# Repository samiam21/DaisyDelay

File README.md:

# DaisyPedal

To get started with programming the ElectroSmith Daisy in Arduino [Getting Started (Arduino Edition) Wiki page!](https://github.com/electro-smith/DaisyWiki/wiki/1a.-Getting-Started-(Arduino-Edition))

## Environment

This project is designed to build with VSCode using the Arduino extension.  It _should_ also build in the Arduino IDE but is untested.

* VS Code - https://code.visualstudio.com/
* VS Code Arduino Extension - https://marketplace.visualstudio.com/items?itemName=vsciot-vscode.vscode-arduino

## Configuration

The files within the .vscode folder may need updated for your environment.  Below is a description of each and what you may need to change.

### arduino.json

This file contains information on the board and connections.

Notes:
* The "output" definition allows VS Code to re-use compiled libraries, rather than needing to compile them every time.
* You will likely need to update the port to reference the COM port on your machine, for when the device is running, not in program mode.
* The "sketch" definition defines which Arduino sketch is compiled.  This project only has a top-level sketch so this should not be modified.

### c_cpp_properties.json

This file contains include paths and other information required for compiling C/C++ code.

Notes:
* You may need to update the "includePath" and "forcedInclude" definitions to point to the correct locations on your machine.

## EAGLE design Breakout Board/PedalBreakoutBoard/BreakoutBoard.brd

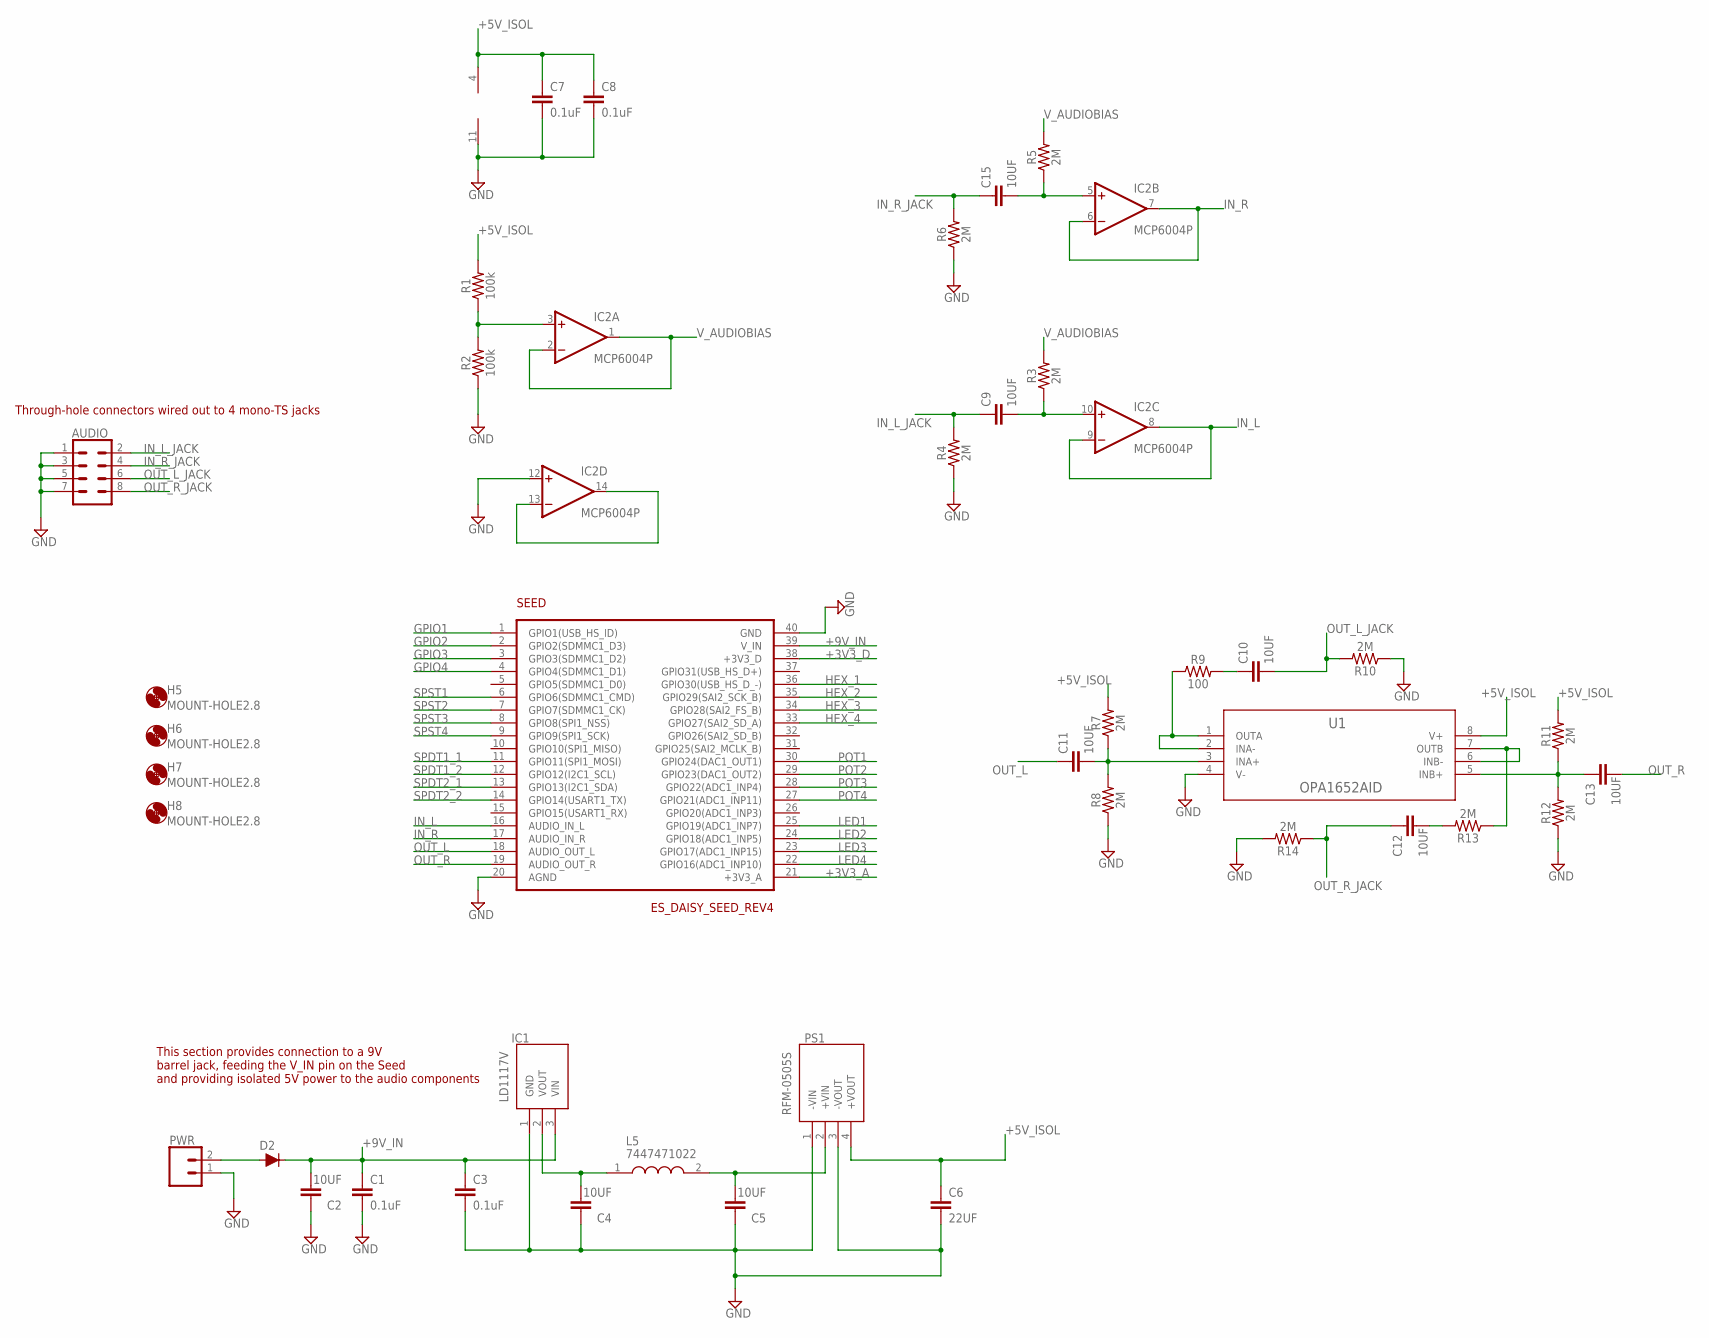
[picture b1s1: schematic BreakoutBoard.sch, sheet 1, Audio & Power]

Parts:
AUDIO: CONN_04X2; 2X4
C1, C3, C7, C8: 0.1uF; CAP-PTH-SMALL-KIT
C2, C4, C5, C9, C10, C11, C12, C13, C15: 10UF; CAP-PTH-SMALL-KIT
C6: 22UF; CAP-PTH-SMALL-KIT
D2: 200mA/100V/1V; DIODE-1N4148
H5, H6, H7, H8: MOUNT-HOLE2.8; 2,8
IC1: LD1117V; TO255P460X1020X2008-3P
IC2: MCP6004P; DIL14
L5: 7447471022; WE-TIS_111190
PS1: RFM-0505S; RFM0505S
PWR: CONN_02; 1X02
R1, R2: 100k; AXIAL-0.3
R3, R4, R5, R6, R7, R8, R10, R11, R12, R13, R14: 2M; AXIAL-0.3
R9: 100; AXIAL-0.3
SEED: ES_DAISY_SEED_REV4; ES_DAISY_SEED
U1: OPA1652AID; D8

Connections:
+3V3_A: SEED.21 (+3V3_A); also elsewhere on the board
+3V3_D: SEED.38 (+3V3_D)
+5V_ISOL: C6.1, C7.1, C8.1, IC2.4 (V+), PS1.4 (+VOUT), R1.P$2 (2), R7.P$2 (2), R11.P$2 (2), U1.8 (V+)
+9V_IN: C1.1, C2.2, C3.1, D2.C, IC1.3 (VIN), SEED.39 (V_IN)
GND: AUDIO.1, AUDIO.3, AUDIO.5, AUDIO.7, C1.2, C2.1, C3.2, C4.1, C5.1, C6.2, C7.2, C8.2, IC1.1 (GND), IC2.11 (V-), IC2.12 (+IN), PS1.1 (-VIN), PS1.3 (-VOUT), PWR.1, R2.P$1 (1), R4.P$1 (1), R6.P$1 (1), R8.P$1 (1), R10.P$1 (1), R12.P$1 (1), R14.P$2 (2), SEED.20 (AGND), SEED.40 (GND), U1.4 (V-); also elsewhere on the board
GPIO1: SEED.1 (GPIO1(USB_HS_ID)); also elsewhere on the board
GPIO2: SEED.2 (GPIO2(SDMMC1_D3)); also elsewhere on the board
GPIO3: SEED.3 (GPIO3(SDMMC1_D2)); also elsewhere on the board
GPIO4: SEED.4 (GPIO4(SDMMC1_D1)); also elsewhere on the board
HEX_1: SEED.36 (GPIO30(USB_HS_D_-)); also elsewhere on the board
HEX_2: SEED.35 (GPIO29(SAI2_SCK_B)); also elsewhere on the board
HEX_3: SEED.34 (GPIO28(SAI2_FS_B)); also elsewhere on the board
HEX_4: SEED.33 (GPIO27(SAI2_SD_A)); also elsewhere on the board
IN_L: IC2.8 (OUT), IC2.9 (-IN), SEED.16 (AUDIO_IN_L)
IN_L_JACK: AUDIO.2, C9.1, R4.P$2 (2)
IN_R: IC2.6 (-IN), IC2.7 (OUT), SEED.17 (AUDIO_IN_R)
IN_R_JACK: AUDIO.4, C15.1, R6.P$2 (2)
LED1: SEED.25 (GPIO19(ADC1_INP7)); also elsewhere on the board
LED2: SEED.24 (GPIO18(ADC1_INP5)); also elsewhere on the board
LED3: SEED.23 (GPIO17(ADC1_INP15)); also elsewhere on the board
LED4: SEED.22 (GPIO16(ADC1_INP10)); also elsewhere on the board
unnamed: D2.A, PWR.2
unnamed: IC2.3 (+IN), R1.P$1 (1), R2.P$2 (2)
unnamed: C5.2, L5.2, PS1.2 (+VIN)
unnamed: C4.2, IC1.2 (VOUT), L5.1
unnamed: C9.2, IC2.10 (+IN), R3.P$1 (1)
unnamed: IC2.13 (-IN), IC2.14 (OUT)
unnamed: C15.2, IC2.5 (+IN), R5.P$1 (1)
unnamed: C11.2, R7.P$1 (1), R8.P$2 (2), U1.3 (INA+)
unnamed: R9.P$1 (1), U1.1 (OUTA), U1.2 (INA-)
unnamed: C10.1, R9.P$2 (2)
unnamed: C13.1, R11.P$1 (1), R12.P$2 (2), U1.5 (INB+)
unnamed: C12.2, R13.P$2 (2)
unnamed: R13.P$1 (1), U1.6 (INB-), U1.7 (OUTB)
OUT_L: C11.1, SEED.18 (AUDIO_OUT_L)
OUT_L_JACK: AUDIO.6, C10.2, R10.P$2 (2)
OUT_R: C13.2, SEED.19 (AUDIO_OUT_R)
OUT_R_JACK: AUDIO.8, C12.1, R14.P$1 (1)
POT1: SEED.30 (GPIO24(DAC1_OUT1)); also elsewhere on the board
POT2: SEED.29 (GPIO23(DAC1_OUT2)); also elsewhere on the board
POT3: SEED.28 (GPIO22(ADC1_INP4)); also elsewhere on the board
POT4: SEED.27 (GPIO21(ADC1_INP11)); also elsewhere on the board
SPDT1_1: SEED.11 (GPIO11(SPI1_MOSI)); also elsewhere on the board
SPDT1_2: SEED.12 (GPIO12(I2C1_SCL)); also elsewhere on the board
SPDT2_1: SEED.13 (GPIO13(I2C1_SDA)); also elsewhere on the board
SPDT2_2: SEED.14 (GPIO14(USART1_TX)); also elsewhere on the board
SPST1: SEED.6 (GPIO6(SDMMC1_CMD)); also elsewhere on the board
SPST2: SEED.7 (GPIO7(SDMMC1_CK)); also elsewhere on the board
SPST3: SEED.8 (GPIO8(SPI1_NSS)); also elsewhere on the board
SPST4: SEED.9 (GPIO9(SPI1_SCK)); also elsewhere on the board
V_AUDIOBIAS: IC2.1 (OUT), IC2.2 (-IN), R3.P$2 (2), R5.P$2 (2)

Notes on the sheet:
Through-hole connectors wired out to 4 mono-TS jacks
This section provides connection to a 9V barrel jack, feeding the V_IN pin on the Seed and providing isolated 5V power to the audio components

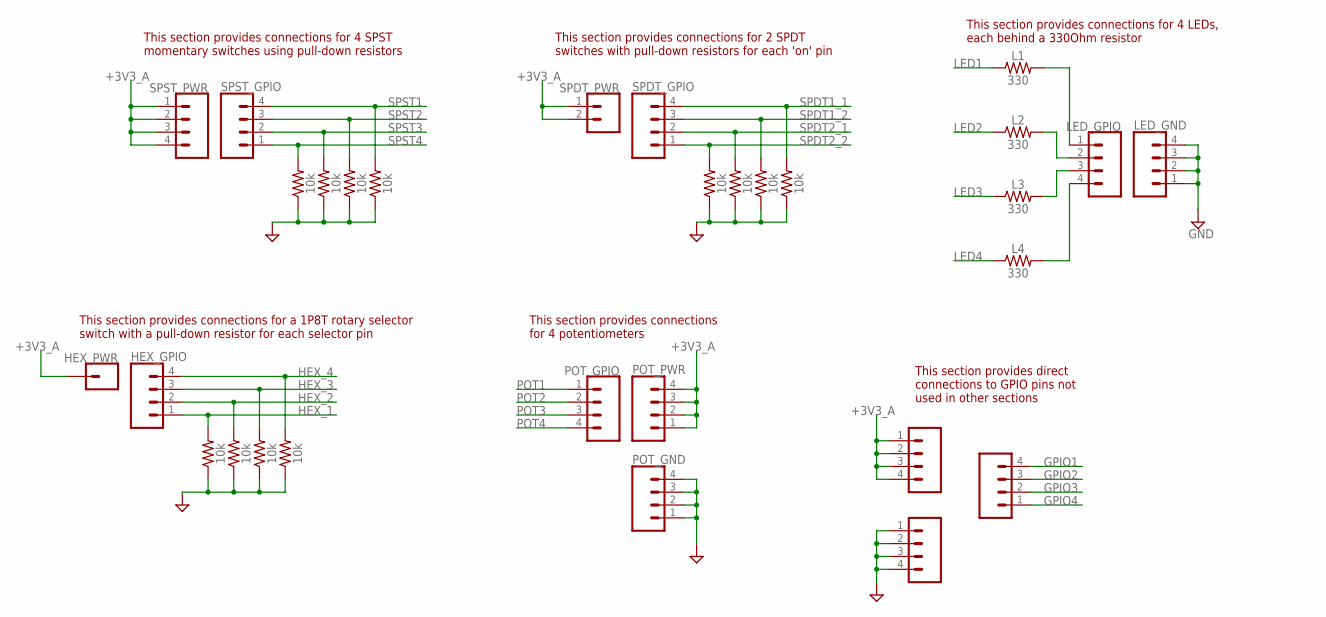
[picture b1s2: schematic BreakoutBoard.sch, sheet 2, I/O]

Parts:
EX_GND: CONN_04; 1X04
EX_GPIOS: CONN_04; 1X04
EX_PWR: CONN_04; 1X04
HEX_GPIO: CONN_04; 1X04
HEX_PWR: CONN_01; 1X01
L1, L2, L3, L4: 330; AXIAL-0.3
LED_GND: CONN_04; 1X04
LED_GPIO: CONN_04; 1X04
POT_GND: CONN_04; 1X04
POT_GPIO: CONN_04; 1X04
POT_PWR: CONN_04; 1X04
R15, R16, R17, R18, R19, R20, R21, R22, R23, R24, R25, R26: 10k; AXIAL-0.3
SPDT_GPIO: CONN_04; 1X04
SPDT_PWR: CONN_02; 1X02
SPST_GPIO: CONN_04; 1X04
SPST_PWR: CONN_04; 1X04

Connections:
+3V3_A: EX_PWR.1, EX_PWR.2, EX_PWR.3, EX_PWR.4, HEX_PWR.1, POT_PWR.1, POT_PWR.2, POT_PWR.3, POT_PWR.4, SPDT_PWR.1, SPDT_PWR.2, SPST_PWR.1, SPST_PWR.2, SPST_PWR.3, SPST_PWR.4; also elsewhere on the board
GND: EX_GND.1, EX_GND.2, EX_GND.3, EX_GND.4, LED_GND.1, LED_GND.2, LED_GND.3, LED_GND.4, POT_GND.1, POT_GND.2, POT_GND.3, POT_GND.4, R15.P$1 (1), R16.P$1 (1), R17.P$1 (1), R18.P$1 (1), R19.P$1 (1), R20.P$1 (1), R21.P$1 (1), R22.P$1 (1), R23.P$1 (1), R24.P$1 (1), R25.P$1 (1), R26.P$1 (1); also elsewhere on the board
GPIO1: EX_GPIOS.4; also elsewhere on the board
GPIO2: EX_GPIOS.3; also elsewhere on the board
GPIO3: EX_GPIOS.2; also elsewhere on the board
GPIO4: EX_GPIOS.1; also elsewhere on the board
HEX_1: HEX_GPIO.1, R23.P$2 (2); also elsewhere on the board
HEX_2: HEX_GPIO.2, R24.P$2 (2); also elsewhere on the board
HEX_3: HEX_GPIO.3, R25.P$2 (2); also elsewhere on the board
HEX_4: HEX_GPIO.4, R26.P$2 (2); also elsewhere on the board
LED1: L1.P$1 (1); also elsewhere on the board
LED2: L2.P$1 (1); also elsewhere on the board
LED3: L3.P$1 (1); also elsewhere on the board
LED4: L4.P$1 (1); also elsewhere on the board
unnamed: L1.P$2 (2), LED_GPIO.1
unnamed: L2.P$2 (2), LED_GPIO.2
unnamed: L3.P$2 (2), LED_GPIO.3
unnamed: L4.P$2 (2), LED_GPIO.4
POT1: POT_GPIO.1; also elsewhere on the board
POT2: POT_GPIO.2; also elsewhere on the board
POT3: POT_GPIO.3; also elsewhere on the board
POT4: POT_GPIO.4; also elsewhere on the board
SPDT1_1: R22.P$2 (2), SPDT_GPIO.4; also elsewhere on the board
SPDT1_2: R21.P$2 (2), SPDT_GPIO.3; also elsewhere on the board
SPDT2_1: R20.P$2 (2), SPDT_GPIO.2; also elsewhere on the board
SPDT2_2: R19.P$2 (2), SPDT_GPIO.1; also elsewhere on the board
SPST1: R18.P$2 (2), SPST_GPIO.4; also elsewhere on the board
SPST2: R17.P$2 (2), SPST_GPIO.3; also elsewhere on the board
SPST3: R16.P$2 (2), SPST_GPIO.2; also elsewhere on the board
SPST4: R15.P$2 (2), SPST_GPIO.1; also elsewhere on the board

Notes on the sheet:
This section provides connections for 2 SPDT switches with pull-down resistors for each 'on' pin
This section provides connections for a 1P8T rotary selector switch with a pull-down resistor for each selector pin
This section provides connections for 4 potentiometers
This section provides connections for 4 SPST momentary switches using pull-down resistors
This section provides connections for 4 LEDs, each behind a 330Ohm resistor
This section provides direct connections to GPIO pins not used in other sections

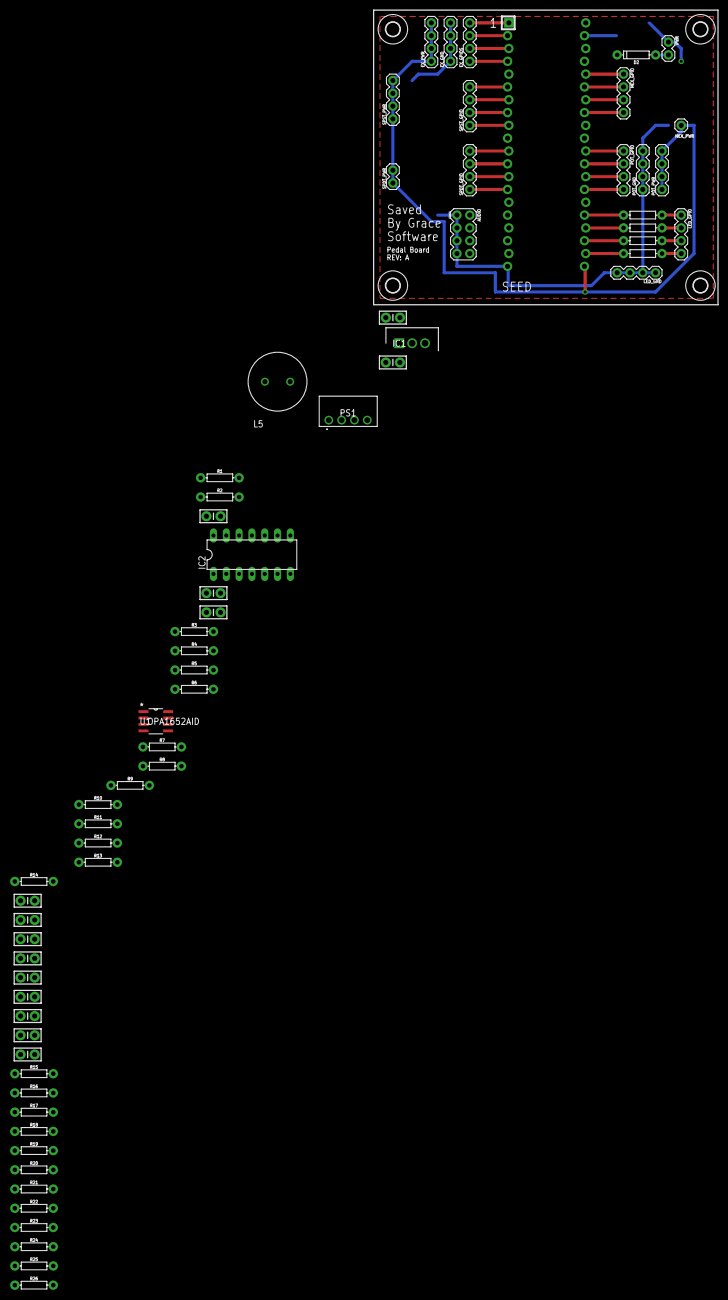
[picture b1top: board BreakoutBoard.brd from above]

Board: 2 copper layers, 68.2 x 58.4 mm, 71 parts (0 on the bottom side), 54 nets.

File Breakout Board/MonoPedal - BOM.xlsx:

Qty | Value | Device | Package | Parts | Description | ARROW_PART_NUMBER | ARROW_PRICE-STOCK | DATASHEET_URL | DESCRIPTION.1 | FAMILY_NAME | GENERIC_PART_NUMBER | HEIGHT | INDUSTRY_STD_PKG_TYPE | IPN | MANUFACTURER | MANUFACTURER_NAME | MANUFACTURER_PART_NUMBER | MOUSER_PART_NUMBER | MOUSER_PRICE-STOCK | PACKAGE_DESIGNATOR | PIN_COUNT | POPULARITY | PROD_ID | VALUE.1 | VENDOR | Column1
6 |  | CONN_01 | 1X01 | HEX_PWR, LED_GND, LED_GPIO, SPDT_PWR, SPST_GPIO, SPST_PWR | Single connection point. Often used as Generic Header-pin footprint for 0.1 inc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
4 |  | CONN_02 | 1X02 | AUD_GND, AUD_PIN, PWR, SPDT_GPIO | Multi connection point. Often used as Generic Header-pin footprint for 0.1 inch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
4 |  | CONN_04 | 1X04 | HEX_GPIO, POT_GND, POT_GPIO, POT_PWR | Multi connection point. Often used as Generic Header-pin footprint for 0.1 inch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 |  |  |  |  |  |  |  |  |  |  |  |  |  |  |  |  |  | CONN-09696
4 | 0.1UF | 0.1UF | CAP-PTH-SMALL-KIT | C1, C3, C5, C7
1 | 100 | 100OHM-HORIZ-1/4W-1% | AXIAL-0.3 | R9 | 100Î© resistor |  |  |  |  |  |  |  |  |  |  |  |  |  |  |  |  |  | RES-12181 | 100
2 | 100k | 100KOHM-HORIZ-1/4W-5% | AXIAL-0.3 | R1, R2 | 100kÎ© resistor |  |  |  |  |  |  |  |  |  |  |  |  |  |  |  |  |  | RES-10686 | 100k
6 | 10UF | 10UF | CAP-PTH-SMALL-KIT | C2, C4, C9, C10, C11, C12
7 | 10k | 10KOHM-HORIZ-1/4W-5% | AXIAL-0.3 | D11, D12, H1, H2, H3, H4, S1 | 10kÎ© resistor |  |  |  |  |  |  |  |  |  |  |  |  |  |  |  |  |  | RES-09435 | 10k
1 | 200mA/100V/1V | DIODE-1N4148 | DIODE-1N4148 | D2 | Diode |  |  |  |  |  |  |  |  |  |  |  |  |  |  |  |  |  | DIO-08378 | 200mA/100V/1V
1 | 22UF | 22UF | CAP-PTH-SMALL-KIT | C6
5 | 2M | 2MOHM-HORIZ-1/4W-5% | AXIAL-0.3 | R3, R4, R7, R8, R10 | 2MÎ© resistor |  |  |  |  |  |  |  |  |  |  |  |  |  |  |  |  |  | RES-09329 | 2M
1 | 330 | 330OHM-HORIZ-1/10W-5% | AXIAL-0.3 | L1 | 330Î© resistor |  |  |  |  |  |  |  |  |  |  |  |  |  |  |  |  |  | RES-8371 | 330
1 | 7447471022 | 7447471022 | WE-TIS_111190 | L5 | Wurth 2.2 uH +/-20% Ferrite Leaded Inductor, Max SRF:75MHz, 10A Idc, 0.009 Rdc 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 |  |  |  | Wurth 2.2 uH +/-20% Ferrite Leaded Inductor, Max SRF:75MHz, 10A Idc, 0.009 Rdc 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 |  |  | mm |  |  |  | Wurth Elektronik | 7447471022 | 710-7447471022 | https://www.mouser.com/Search/Refine.aspx?Keyword=710-7447471022
1 | ES_DAISY_SEED_REV4 | ES_DAISY_SEED_REV4 | ES_DAISY_SEED | SEED |  |  |  |  |  |  |  |  |  | Daisy Seed
1 | LD1117V | LD1117V | TO255P460X1020X2008-3P | IC1 | I.C. LD1117V | LD1117V | https://www.arrow.com/en/products/ld1117v/stmicroelectronics |  | I.C. LD1117V |  |  | 4.6mm |  |  |  | STMicroelectronics | LD1117V | 511-LD1117V | https://www.mouser.co.uk/ProductDetail/STMicroelectronics/LD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
1 | MCP6004P | MCP6004P | DIL14 | IC2 | Quad Op Amp 2.7V to 6.0V Single Supply CMOS |  |  |  |  |  |  |  |  |  |  |  |  |  |  |  |  | 0
4 | MOUNT-HOLE2.8 | MOUNT-HOLE2.8 | 2,8 | H5, H6, H7, H8 | MOUNTING HOLE with drill center marker |  |  |  |  |  |  |  |  |  |  |  |  |  |  |  |  | 15
1 | OPA1652AID | OPA1652AID | D8 | U1 |  |  |  | http://www.ti.com/lit/gpn/OPA1652 | Sound Plus Low Noise and Distortion, General-Purpose, FET-Input Audio Op Amps | LOW NOISE | OPA1652 |  | SOIC |  | Texas Instruments |  | OPA1652AID |  |  | D | 8 |  |  |  | Texas Instruments
1 | RFM-0505S | RFM-0505S | RFM0505S | PS1 | RECOM POWER - RFM-0505S - DC-DC CONVERTER, 5V, 0.2A |  |  |  | RECOM POWER - RFM-0505S - DC-DC CONVERTER, 5V, 0.2A |  |  | 10.5mm |  |  |  | RECOM Power | RFM-0505S | 919-RFM-0505S | https://www.mouser.co.uk/ProductDetail/RECOM-Power/RFM-0505S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

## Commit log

2020-10-28 DP-17 - Add single echo effect
2020-10-28 DP-15 - Working on reading type switcher SPDT
2020-10-29 DP-15 - Switch delay type with SPDT switch
2020-10-29 DP-15 - Add delay type
2020-11-05 Rename main sketch file
2020-11-12 DP-24 - Convert DaisyDelay to use platform io
2020-11-18 DP-24 - Fix merge issues
2020-11-18 DP-25 - Initialize type in setup
2020-11-18 DP-25 - Fix interrupt issue for effect selector
2020-11-19 DP-25 - Disable selector
2020-11-26 DP-30 - Use class for toggle
2020-11-28 DP-30 - Switch to using knob class
2020-12-11 DP-30 - Update to using Button class
2020-12-11 DP-31 - Add volume boost knob
2021-01-11 Update block size to smallest to remove noise
2021-01-11 Code cleanup
2021-01-13 Update volume boost
2021-01-15 Update to define pin config
2021-01-16 Update pins for release board
2021-01-17 Swap pot ranges because of backwards wiring

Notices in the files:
parts and their libraries:
SparkFun-Connectors: Licensing: Creative Commons ShareAlike 4.0 International - https://creativecommons.org/licenses/by-sa/4.0
